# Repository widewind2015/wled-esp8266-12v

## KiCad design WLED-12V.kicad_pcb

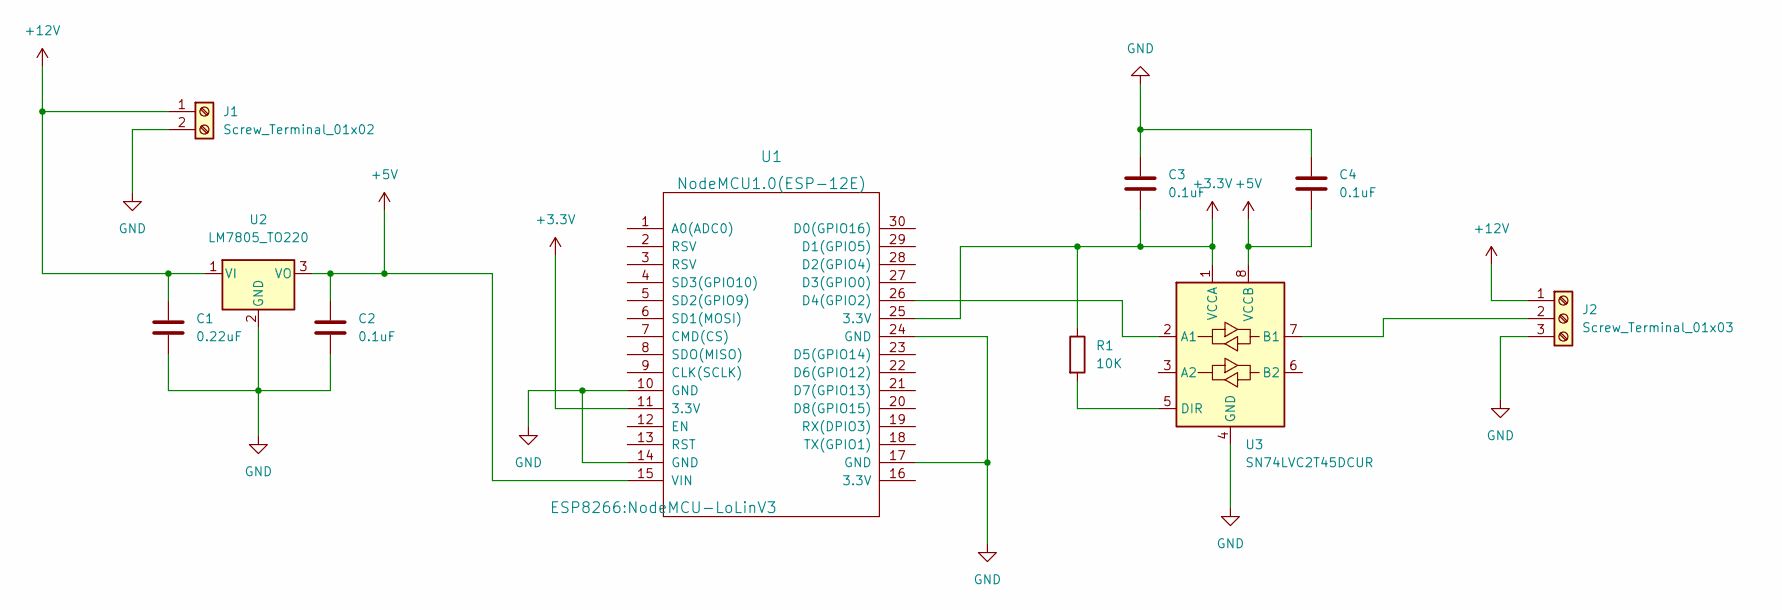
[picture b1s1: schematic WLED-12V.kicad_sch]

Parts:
C1: 0.22uF; C_0805_2012Metric
C2, C3, C4: 0.1uF; C_0805_2012Metric
J1: Screw_Terminal_01x02; TerminalBlock_MetzConnect_Type055_RT01502HDWU_1x02_P5.00mm_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
J2: Screw_Terminal_01x03; TerminalBlock_MetzConnect_Type055_RT01503HDWU_1x03_P5.00mm_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
R1: 10K; R_0805_2012Metric
U1: NodeMCU1.0(ESP-12E); NodeMCU-LoLinV3
U2: LM7805_TO220; TO-220-3_Vertical
U3: SN74LVC2T45DCUR; VSSOP-8_2.4x2.1mm_P0.5mm

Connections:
+3.3V: C3.2, R1.1, U1.11 (3.3V), U1.25 (3.3V), U3.1 (VCCA)
+5V: C2.1, C4.2, U1.15 (VIN), U2.3 (VO), U3.8 (VCCB)
+12V: C1.1, J1.1, J2.1, U2.1 (VI)
GND: C1.2, C2.2, C3.1, C4.1, J1.2, J2.3, U1.10 (GND), U1.14 (GND), U1.17 (GND), U1.24 (GND), U2.2 (GND), U3.4 (GND)
unnamed: J2.2, U3.7 (B1)
unnamed: R1.2, U3.5 (DIR)
unnamed: U1.26 (D4(GPIO2)), U3.2 (A1)

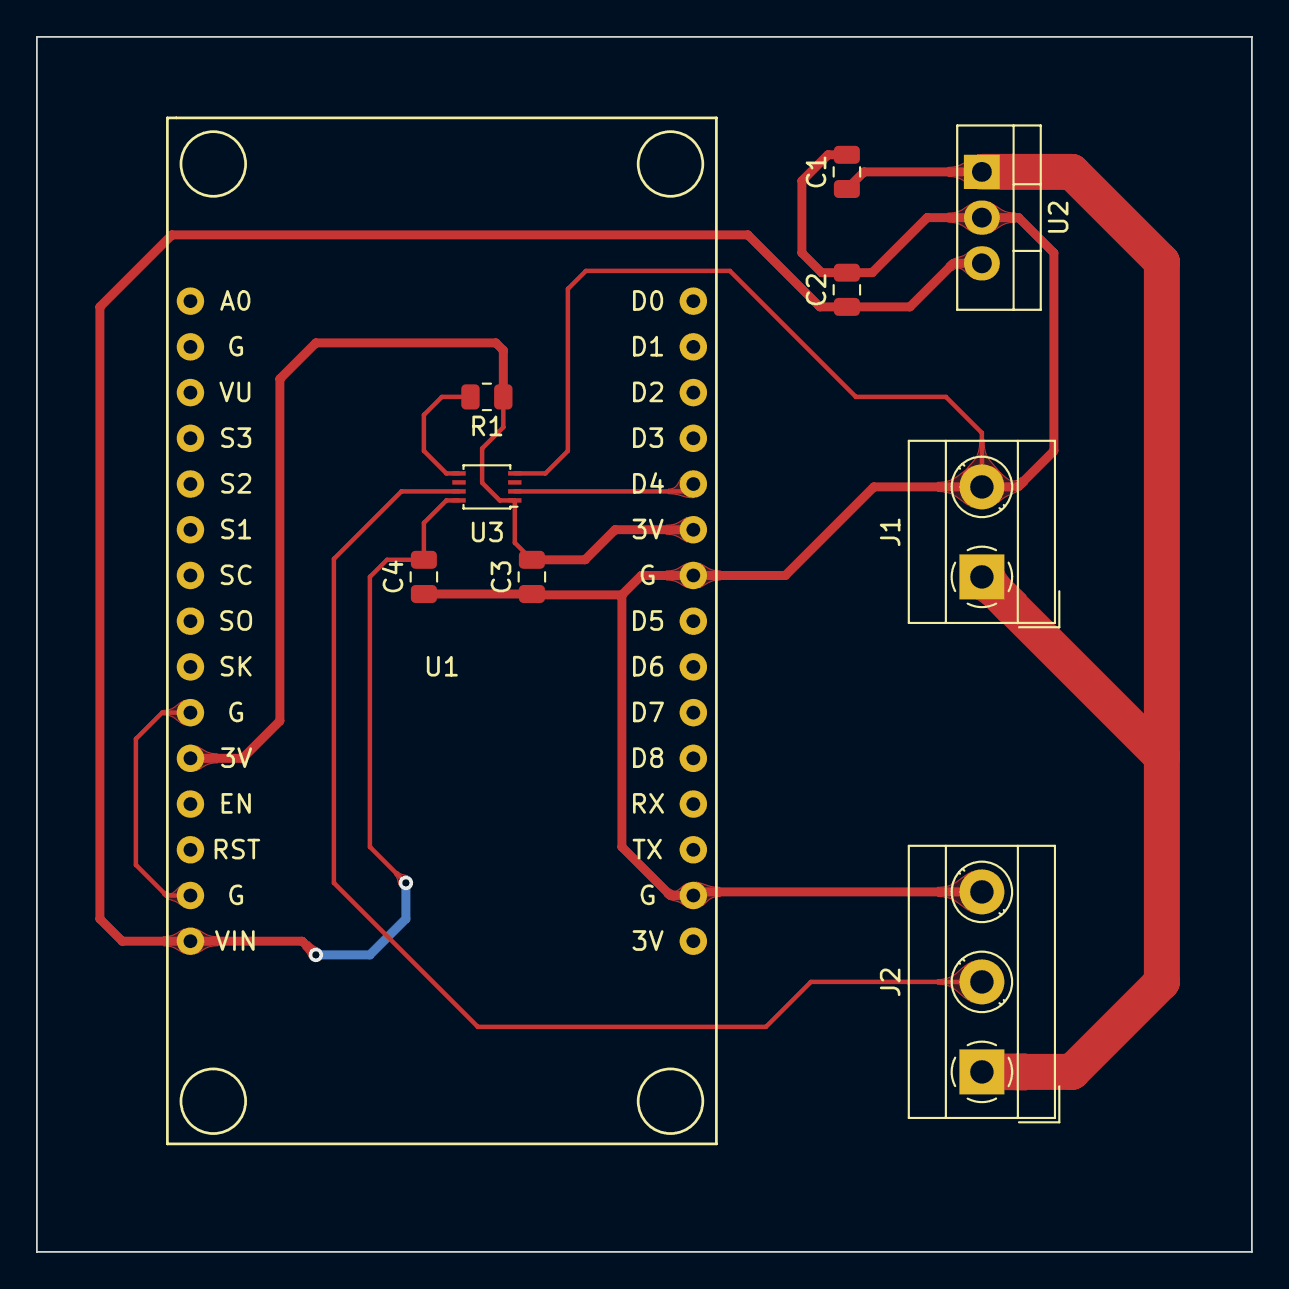
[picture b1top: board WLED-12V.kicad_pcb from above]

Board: 2 copper layers, 67.5 x 67.5 mm, 10 parts (0 on the bottom side), 7 nets.

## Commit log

2022-10-23 first upload
